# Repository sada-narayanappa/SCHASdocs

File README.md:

SCH
===

Smart and Connected Health Application
HI Eric

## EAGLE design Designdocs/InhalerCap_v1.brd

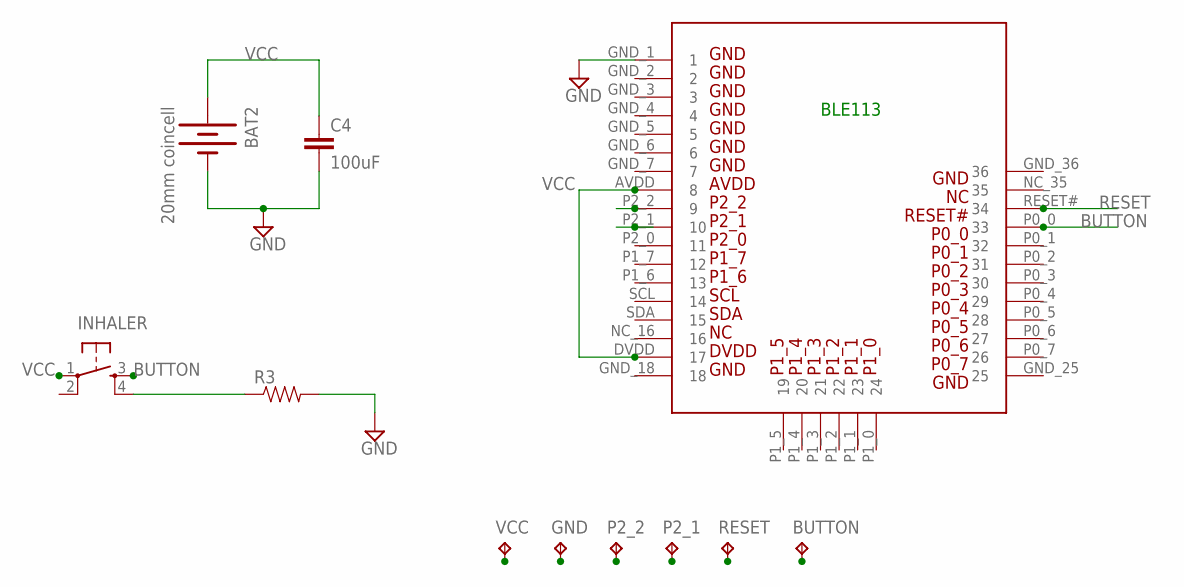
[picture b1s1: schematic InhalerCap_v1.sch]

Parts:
BAT2: 20mm coincell; BATTCON_20MM_4LEGS
BUTTON: TPTP20SQ; TP20SQ
C4: 100uF; 1206
GND: TPTP20SQ; TP20SQ
INHALER: TAC_SWITCHSMD; TACTILE_SWITCH_SMD
P2_1, P2_2: TPTP20SQ; TP20SQ
R3: RESISTOR0603-RES; 0603-RES
RESET: TPTP20SQ; TP20SQ
U$1: BLE113-A
VCC: TPTP20SQ; TP20SQ

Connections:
1: INHALER.4, R3.1
BUTTON: BUTTON.TP, INHALER.3, U$1.P0_0 (33)
GND: BAT2.2 (-), C4.2, GND.TP, R3.2, U$1.GND_1 (1)
P2_1: P2_1.TP, U$1.P2_1 (10)
P2_2: P2_2.TP, U$1.P2_2 (9)
RESET: RESET.TP, U$1.RESET# (34)
VCC: BAT2.1 (+), C4.1, INHALER.1, U$1.AVDD (8), U$1.DVDD (17), VCC.TP

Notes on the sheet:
BLE113

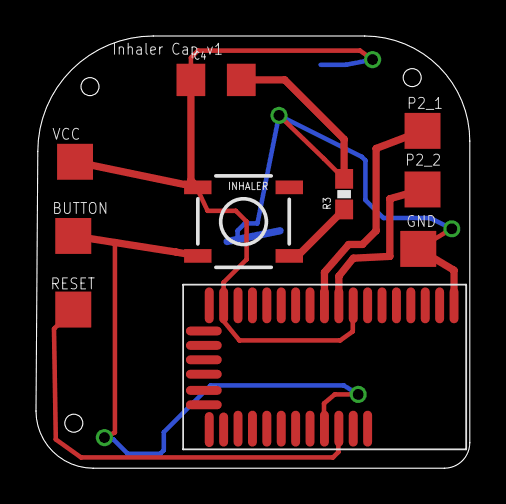
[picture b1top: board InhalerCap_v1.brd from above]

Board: 2 copper layers, 24.1 x 24.0 mm, 11 parts (1 on the bottom side), 7 nets.

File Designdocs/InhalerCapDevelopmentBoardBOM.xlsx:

Name | Price | Quantity | Total | Link
BLE113 | 15.38 | 1 | 15.38 | http://www.digikey.com/product-detail/en/BLE113-A-M256K/1446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
Voltage Regulator LB33 | 0.79500000000000004 | 1 | 0.79500000000000004 | https://www.sparkfun.com/products/11253
Micro USB | 1.5 | 1 | 1.5 | https://www.sparkfun.com/products/8533
Coin Cell Holder | 0.95 | 1 | 0.95 | https://www.sparkfun.com/products/11892
Coin Cell Battery | 1.95 | 1 | 1.95 | https://www.sparkfun.com/products/338
Switch | 1.5 | 2 | 3 | https://www.sparkfun.com/products/597
LED | 0.16 | 1 | 0.16 | http://www.digikey.com/product-detail/en/APT1608SGC/754-1121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
100uF Capacitor | 0.81 | 1 | 0.81 | http://www.digikey.com/product-detail/en/GRM31CR60J107ME39K/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
.47uF Capacitor | 0.11 | 3 | 0.33 | http://www.digikey.com/product-detail/en/UMK107ABJ474KA-T/58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
10k Resistor | 0.1 | 1 | 0.1 | http://www.digikey.com/product-detail/en/ERJ-3GEYJ103V/P10KG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
4.7k Resistor | 0.1 | 4 | 0.4 | http://www.digikey.com/product-detail/en/ERJ-3GEYJ472V/P4.7K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
220 Resistor | 0.1 | 1 | 0.1 | http://www.digikey.com/product-detail/en/MCR03ERTF2200/RHM22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
1x8 Pin Header | 0.5 | 1 | 0.5 | https://www.sparkfun.com/products/9279
1x6 Pin Header | 0.5 | 1 | 0.5 | https://www.sparkfun.com/products/9280
2x3 Pin Header | 1.5 | 1 | 1.5 | https://www.sparkfun.com/products/10877

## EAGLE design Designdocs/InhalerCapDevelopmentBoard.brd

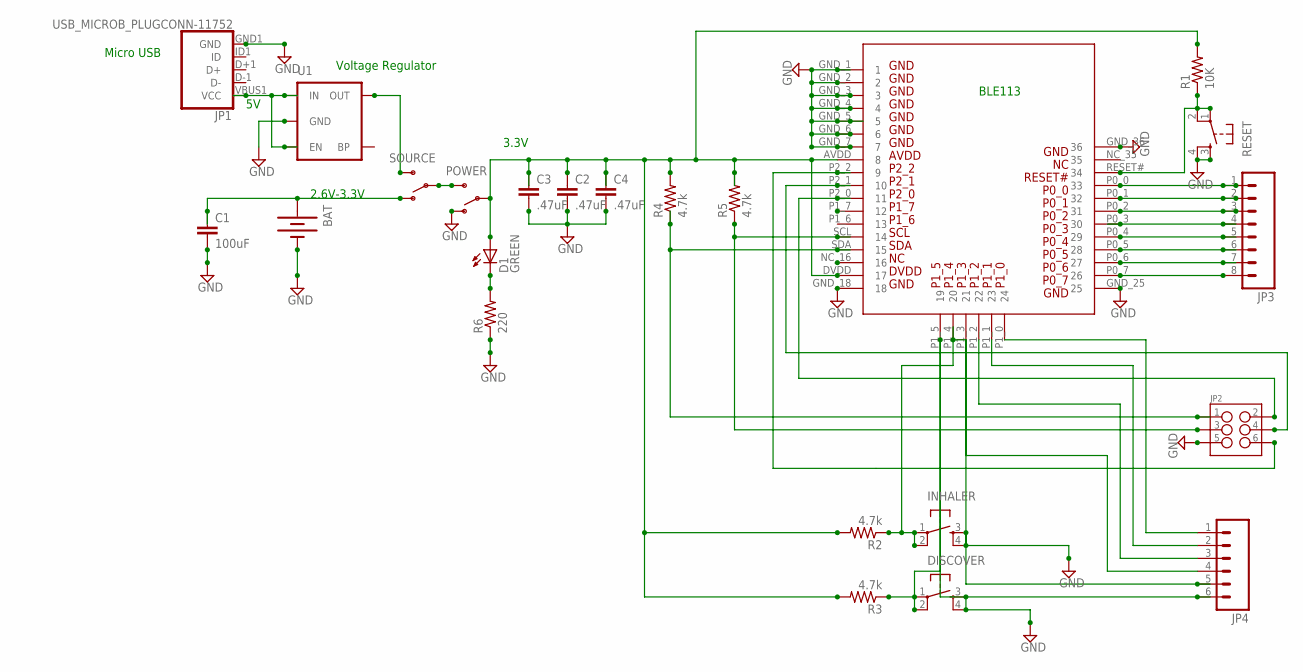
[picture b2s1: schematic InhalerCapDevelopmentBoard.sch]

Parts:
BAT: BATTERY20SMD; BATTCON_20MM
BLE113: BLE113-A
C1: 100uF; 0603-CAP
C2, C3, C4: .47uF; 0603-CAP
D1: GREEN; LED-0603
DISCOVER: TAC_SWITCHSMD; TACTILE_SWITCH_SMD
INHALER: TAC_SWITCHSMD; TACTILE_SWITCH_SMD
JP1: USB_MICROB_PLUGCONN-11752; USB-B-MICRO-SMD_V03
JP2: M03X2SHROUD; 2X3-SHROUDED
JP3: M08; 1X08_PIN1_NO_SILK
JP4: M06NO_SILK; 1X06_NO_SILK
POWER: SWITCH-SPDTSMD; AYZ0202
R1: 10K; 0603-RES
R2, R3, R4, R5: 4.7k; 0603-RES
R6: 220; 0603-RES
RESET: TAC_SWITCHSMD; TACTILE_SWITCH_SMD
SOURCE: SWITCH-SPDTSMD; AYZ0202
U1: MIC52053.3V; SOT23-5

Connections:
GND: BAT.2 (-), BLE113.GND_1 (1), BLE113.GND_2 (2), BLE113.GND_3 (3), BLE113.GND_4 (4), BLE113.GND_5 (5), BLE113.GND_6 (6), BLE113.GND_7 (7), BLE113.GND_18 (18), BLE113.GND_25 (25), BLE113.GND_36 (36), C1.2, C2.2, C3.2, C4.2, DISCOVER.3, DISCOVER.4, INHALER.3, INHALER.4, JP1.GND1 (GND), JP2.5, POWER.1 (O), R6.1, RESET.3, RESET.4, U1.2 (GND)
unnamed: BLE113.P1_4 (20), INHALER.1, INHALER.2, JP4.5, R2.1
unnamed: BLE113.AVDD (8), BLE113.DVDD (17), C2.1, C3.1, C4.1, D1.A, POWER.2, R1.2, R2.2, R3.2, R4.2, R5.2
unnamed: POWER.3 (S), SOURCE.2
unnamed: BAT.1 (+), C1.1, SOURCE.1 (O)
unnamed: SOURCE.3 (S), U1.5 (OUT)
unnamed: JP1.VBUS1 (VCC), U1.1 (IN), U1.3 (EN)
unnamed: BLE113.RESET# (34), R1.1, RESET.1, RESET.2
unnamed: BLE113.P0_6 (27), JP3.7
unnamed: BLE113.P0_4 (29), JP3.5
unnamed: BLE113.P1_2 (22), JP4.3
unnamed: BLE113.P1_5 (19), DISCOVER.1, DISCOVER.2, JP4.6, R3.1
unnamed: BLE113.SDA (15), JP2.1, R4.1
unnamed: BLE113.SCL (14), JP2.3, R5.1
unnamed: D1.C, R6.2
unnamed: BLE113.P1_0 (24), JP4.1
unnamed: BLE113.P0_0 (33), JP3.1
unnamed: BLE113.P1_1 (23), JP4.2
unnamed: BLE113.P0_1 (32), JP3.2
unnamed: BLE113.P2_0 (11), JP2.2
unnamed: BLE113.P2_1 (10), JP2.4
unnamed: BLE113.P2_2 (9), JP2.6
unnamed: BLE113.P0_2 (31), JP3.3
unnamed: BLE113.P1_3 (21), JP4.4
unnamed: BLE113.P0_3 (30), JP3.4
unnamed: BLE113.P0_5 (28), JP3.6
unnamed: BLE113.P0_7 (26), JP3.8

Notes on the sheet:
BLE113
Micro USB
Voltage Regulator
3.3V
2.6V-3.3V

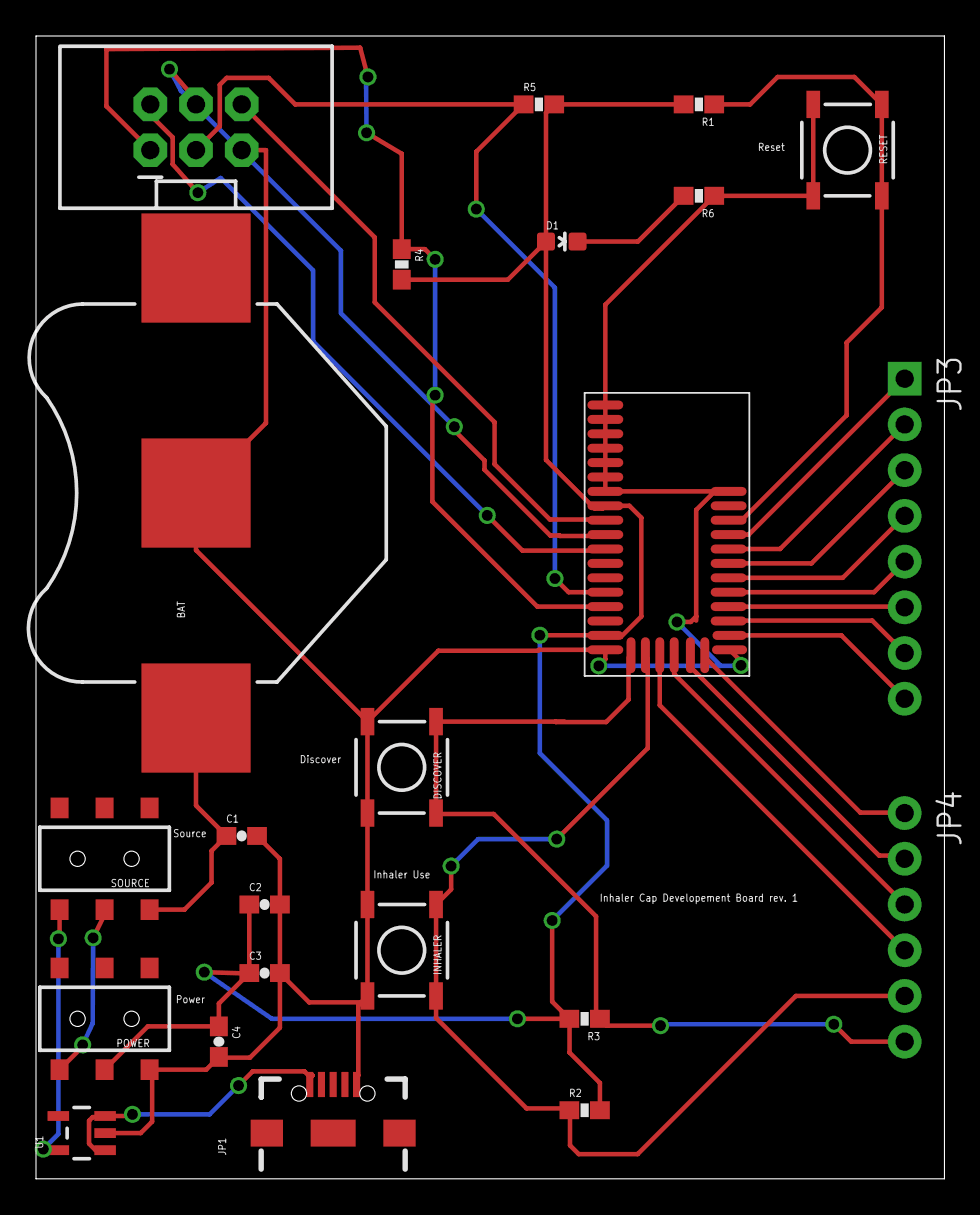
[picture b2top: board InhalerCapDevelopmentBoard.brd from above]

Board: 2 copper layers, 50.5 x 63.5 mm, 23 parts (0 on the bottom side), 27 nets.

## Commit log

2015-01-16 Commiting by Sada
2015-01-26 updating db_design.docx
2015-02-04 Updated Schematic
2015-02-06 Updated Board and Schematic
2015-02-12 Rev. 1 of board
2015-02-13 Rev. 2 Of Development Board
2015-02-20 Updated design docs 2/20/15
2015-02-27 Created cap schematic
2015-03-08 Open Weather data requests
    Put file descriptions for the open weather data requests.
2015-03-08 OpenWeather data request
    File descriptions for the open weather data request.
2015-03-27 Added pin connection information
2015-04-02 Design for simplified inhaler cap
2015-04-06 Added prototype wiring and functionality
2015-04-10 Shipped board
2015-05-14 Updated documentation
2016-10-12 Added Inhaler Cap Documentation

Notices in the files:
parts and their libraries:
SparkFun-Electromechanical: Licensing: Creative Commons ShareAlike 4.0 International - https://creativecommons.org/licenses/by-sa/4.0
